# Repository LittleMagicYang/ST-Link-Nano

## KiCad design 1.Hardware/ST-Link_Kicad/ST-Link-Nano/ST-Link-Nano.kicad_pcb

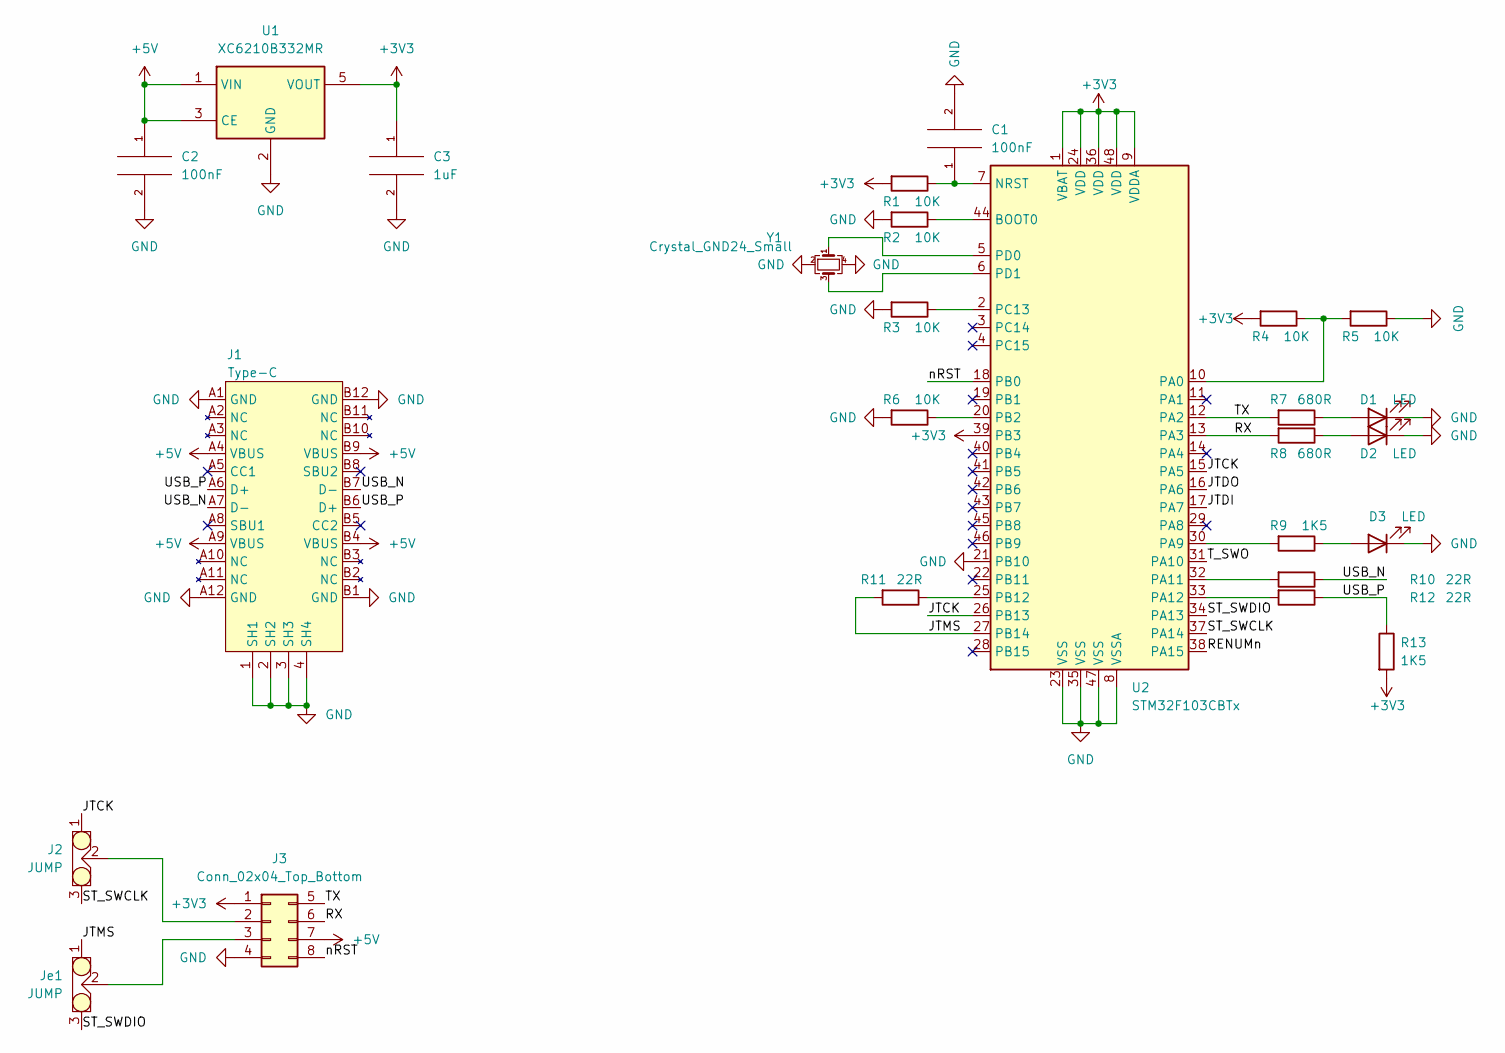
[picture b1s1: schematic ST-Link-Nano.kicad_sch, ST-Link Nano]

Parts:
C1, C2: 100nF; C_0402_1005Metric
C3: 1uF; C_0402_1005Metric
D1, D2, D3: LED; LED_0402_1005Metric
J1: Type-C; TYPE-CF-16P-RAT-L7.5W
J2: JUMP; SMD_JUMP
J3: Conn_02x04_Top_Bottom; SMD_PIN_2x4_TOP_BOTTOM
Je1: JUMP; SMD_JUMP
R1, R2, R3, R4, R5, R6: 10K; R_0402_1005Metric
R7, R8: 680R; R_0402_1005Metric
R9, R13: 1K5; R_0402_1005Metric
R10, R11, R12: 22R; R_0402_1005Metric
U1: XC6210B332MR; SOT-23-5
U2: STM32F103CBTx; LQFP-48_7x7mm_P0.5mm
Y1: Crystal_GND24_Small; Crystal_SMD_3225-4Pin_3.2x2.5mm

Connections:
+3V3: C3.1, J3.1, R1.2, R4.2, R13.2, U1.5 (VOUT), U2.1 (VBAT), U2.9 (VDDA), U2.24 (VDD), U2.36 (VDD), U2.39 (PB3), U2.48 (VDD)
+5V: C2.1, J1.A4 (VBUS), J1.A9 (VBUS), J1.B4 (VBUS), J1.B9 (VBUS), J3.7, U1.1 (VIN), U1.3 (CE)
/JTCK: J2.1, U2.15 (PA5), U2.26 (PB13)
/JTDI: U2.17 (PA7)
/JTDO: U2.16 (PA6)
/JTMS: Je1.1, R11.2, U2.27 (PB14)
/RENUMn: U2.38 (PA15)
/RX: J3.6, R8.2, U2.13 (PA3)
/ST_SWCLK: J2.3, U2.37 (PA14)
/ST_SWDIO: Je1.3, U2.34 (PA13)
/TX: J3.5, R7.2, U2.12 (PA2)
/T_SWO: U2.31 (PA10)
/USB_N: J1.A7 (D-), J1.B7 (D-), R10.1
/USB_P: J1.A6 (D+), J1.B6 (D+), R12.1, R13.1
/nRST: J3.8, U2.18 (PB0)
GND: C1.2, C2.2, C3.2, D1.1 (K), D2.1 (K), D3.1 (K), J1.1 (SH1), J1.2 (SH2), J1.3 (SH3), J1.4 (SH4), J1.A1 (GND), J1.A12 (GND), J1.B1 (GND), J1.B12 (GND), J3.4, R2.2, R3.2, R5.1, R6.2, U1.2 (GND), U2.8 (VSSA), U2.21 (PB10), U2.23 (VSS), U2.35 (VSS), U2.47 (VSS), Y1.2, Y1.4
unnamed: C1.1, R1.1, U2.7 (NRST)
unnamed: D1.2 (A), R7.1
unnamed: D2.2 (A), R8.1
unnamed: D3.2 (A), R9.1
unnamed: J2.2, J3.2
unnamed: J3.3, Je1.2
unnamed: R2.1, U2.44 (BOOT0)
unnamed: R3.1, U2.2 (PC13)
unnamed: R4.1, R5.2, U2.10 (PA0)
unnamed: R6.1, U2.20 (PB2)
unnamed: R9.2, U2.30 (PA9)
unnamed: R10.2, U2.32 (PA11)
unnamed: R11.1, U2.25 (PB12)
unnamed: R12.2, U2.33 (PA12)
unnamed: U2.5 (PD0), Y1.1
unnamed: U2.6 (PD1), Y1.3

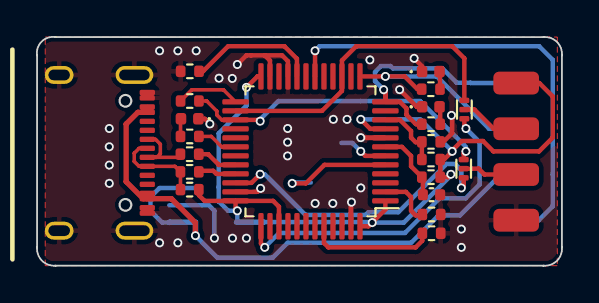
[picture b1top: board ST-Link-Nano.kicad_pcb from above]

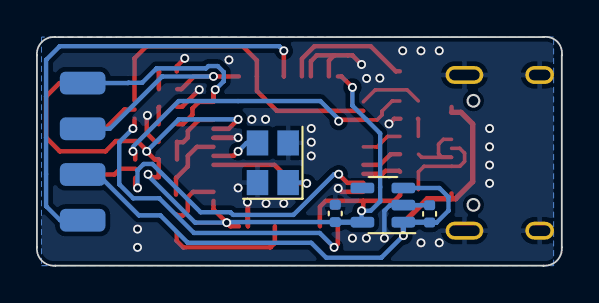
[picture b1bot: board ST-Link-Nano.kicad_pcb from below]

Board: 2 copper layers, 29.2 x 12.7 mm, 26 parts (4 on the bottom side), 28 nets.

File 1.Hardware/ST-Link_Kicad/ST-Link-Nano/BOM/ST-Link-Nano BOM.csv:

"ID";"指示符";"软件包";"数量";"名称";"供应商和参考";
1;"D1,D2,D3";"LED_0402_1005Metric";3;"LED";;;
2;"R1,R2,R6,R4,R3,R5";"R_0402_1005Metric";6;"10K";;;
3;"R10,R11,R12";"R_0402_1005Metric";3;"22R";;;
4;"J1";"TYPE-CF-16P-RAT-L7.5W";1;"Type-C";;;
5;"R9,R13";"R_0402_1005Metric";2;"1K5";;;
6;"J3";"SMD_PIN_2x4_TOP_BOTTOM";1;"Conn_02x04_Top_Bottom";;;
7;"Je1,J2";"SMD_JUMP";2;"JUMP";;;
8;"R8,R7";"R_0402_1005Metric";2;"680R";;;
9;"U2";"LQFP-48_7x7mm_P0.5mm";1;"STM32F103CBTx";;;
10;"C1,C2";"C_0402_1005Metric";2;"100nF";;;
11;"Y1";"Crystal_SMD_3225-4Pin_3.2x2.5mm";1;"Crystal_GND24_Small";;;
12;"C3";"C_0402_1005Metric";1;"1uF";;;
13;"U1";"SOT-23-5";1;"XC6210B332MR";;;

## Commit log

2022-07-30 2022.7.30 在kicad中画ST-Link的原理图和PCB. 部分元件要自己画封装。
2022-07-31 在Kicad中画ST-Link的PCB，画到差不多一半
    大概已经用了3～4小时，比想象中的要慢一些，第一次用Kicad画还不太熟
2022-08-07 已完成PCB，输出Gerber文件
    2022/8/7
    今天把之前剩下一半的PCB画完了，输出了Gerber，准备到嘉立创打样，然后在淘宝上买器件回来自己焊接。
2022-08-07 修改生成的BOM表
2022-10-09 导出丝印
    方便焊接
